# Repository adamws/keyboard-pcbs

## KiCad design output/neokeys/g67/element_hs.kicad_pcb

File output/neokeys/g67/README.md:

## neokeys/g67/element_hs

[layout](element_hs-kle.json) - [PCB](element_hs.kicad_pcb)

{:loading="lazy"}

[Open in keyboard-layout-editor](http://www.keyboard-layout-editor.com/##@@_c=#777777;&=0,0&_c=#cccccc;&=0,1&=0,2&=0,3&=0,4&=0,5&=0,6&=0,7&=0,8&=0,9&=0,10&=0,11&=0,12&_c=#aaaaaa&w:2;&=0,13&=0,14;&@_w:1.5;&=1,0&_c=#cccccc;&=1,1&=1,2&=1,3&=1,4&=1,5&=1,6&=1,7&=1,8&=1,9&=1,10&=1,11&=1,12&_w:1.5;&=1,13&_c=#aaaaaa;&=1,14;&@_w:1.75;&=2,0&_c=#cccccc;&=2,1&=2,2&=2,3&=2,4&=2,5&=2,6&=2,7&=2,8&=2,9&=2,10&=2,11&_c=#777777&w:2.25;&=2,13&_c=#aaaaaa;&=2,14;&@_w:2.25;&=3,0&_c=#cccccc;&=3,2&=3,3&=3,4&=3,5&=3,6&=3,7&=3,8&=3,9&=3,10&=3,11&_c=#aaaaaa&w:1.75;&=3,12&_c=#777777;&=3,13&_c=#aaaaaa;&=3,14;&@_w:1.25;&=4,0&_w:1.25;&=4,1&_w:1.25;&=4,3&_c=#777777&w:6.25;&=4,6&_c=#aaaaaa&w:1.25;&=4,10&_w:1.25;&=4,11&_x:0.5&c=#777777;&=4,12&=4,13&=4,14)

{:loading="lazy"}

## neokeys/g67/hotswap

[layout](hotswap-kle.json) - [PCB](hotswap.kicad_pcb)

{:loading="lazy"}

[Open in keyboard-layout-editor](http://www.keyboard-layout-editor.com/##@@_c=#777777;&=0,0&_c=#cccccc;&=0,1&=0,2&=0,3&=0,4&=0,5&=0,6&=0,7&=0,8&=0,9&=0,10&=0,11&=0,12&_c=#aaaaaa&w:2;&=0,13&=0,14;&@_w:1.5;&=1,0&_c=#cccccc;&=1,1&=1,2&=1,3&=1,4&=1,5&=1,6&=1,7&=1,8&=1,9&=1,10&=1,11&=1,12&_w:1.5;&=1,13&_c=#aaaaaa;&=1,14;&@_w:1.75;&=2,0&_c=#cccccc;&=2,1&=2,2&=2,3&=2,4&=2,5&=2,6&=2,7&=2,8&=2,9&=2,10&=2,11&_c=#777777&w:2.25;&=2,13&_c=#aaaaaa;&=2,14;&@_w:2.25;&=3,0&_c=#cccccc;&=3,2&=3,3&=3,4&=3,5&=3,6&=3,7&=3,8&=3,9&=3,10&=3,11&_c=#aaaaaa&w:1.75;&=3,12&_c=#777777;&=3,13&_c=#aaaaaa;&=3,14;&@_w:1.25;&=4,0&_w:1.25;&=4,1&_w:1.25;&=4,3&_c=#777777&w:6.25;&=4,6&_c=#aaaaaa&w:1.25;&=4,10&_w:1.25;&=4,11&_x:0.5&c=#777777;&=4,12&=4,13&=4,14)

{:loading="lazy"}

## neokeys/g67/soldered

[layout](soldered-kle.json) - [PCB](soldered.kicad_pcb)

{:loading="lazy"}

[Open in keyboard-layout-editor](http://www.keyboard-layout-editor.com/##@@_x:2.75&y:1.5&c=#777777;&=0,0&_c=#cccccc;&=0,1&=0,2&=0,3&=0,4&=0,5&=0,6&=0,7&=0,8&=0,9&=0,10&=0,11&=0,12&_c=#aaaaaa&w:2;&=0,13%0A%0A%0A0,0&=0,15;&@_x:2.75&w:1.5;&=1,0&_c=#cccccc;&=1,1&=1,2&=1,3&=1,4&=1,5&=1,6&=1,7&=1,8&=1,9&=1,10&=1,11&=1,12&_w:1.5;&=1,14%0A%0A%0A1,0&_c=#aaaaaa;&=1,15;&@_x:2.75&w:1.75;&=2,0&_c=#cccccc;&=2,1&=2,2&=2,3&=2,4&=2,5&=2,6&=2,7&=2,8&=2,9&=2,10&=2,11&_c=#777777&w:2.25;&=2,13%0A%0A%0A1,0&_c=#aaaaaa;&=2,15;&@_x:2.75&w:2.25;&=3,0%0A%0A%0A2,0&_c=#cccccc;&=3,2&=3,3&=3,4&=3,5&=3,6&=3,7&=3,8&=3,9&=3,10&=3,11&_c=#aaaaaa&w:1.75;&=3,12&_c=#777777;&=3,14&_c=#aaaaaa;&=3,15;&@_x:2.75&w:1.25;&=4,0%0A%0A%0A3,0&_w:1.25;&=4,1%0A%0A%0A3,0&_w:1.25;&=4,2%0A%0A%0A3,0&_c=#777777&w:6.25;&=4,7%0A%0A%0A3,0&_c=#aaaaaa&w:1.25;&=4,8%0A%0A%0A3,0&_w:1.25;&=4,9%0A%0A%0A3,0&_x:0.5&c=#777777;&=4,12&=4,13&=4,15;&@_x:15.75&y:-6.5&c=#aaaaaa;&=0,13%0A%0A%0A0,1&=0,14%0A%0A%0A0,1;&@_x:20.25&y:1.5&c=#777777&w:1.25&h:2&w2:1.5&h2:1&x2:-0.25;&=2,13%0A%0A%0A1,1;&@_x:19.25&c=#cccccc;&=2,12%0A%0A%0A1,1;&@_c=#aaaaaa&w:1.25;&=3,0%0A%0A%0A2,1&_c=#cccccc;&=3,1%0A%0A%0A2,1;&@_x:2.75&y:1.5&c=#aaaaaa&w:1.5;&=4,0%0A%0A%0A3,1&=4,1%0A%0A%0A3,1&_w:1.5;&=4,2%0A%0A%0A3,1&_c=#777777&w:7;&=4,7%0A%0A%0A3,1&_c=#aaaaaa&w:1.5;&=4,9%0A%0A%0A3,1;&@_x:2.75&w:1.25;&=4,0%0A%0A%0A3,2&_w:1.25;&=4,1%0A%0A%0A3,2&_w:1.25;&=4,2%0A%0A%0A3,2&_c=#777777&w:6.25;&=4,7%0A%0A%0A3,2&_c=#aaaaaa;&=4,8%0A%0A%0A3,2&=4,9%0A%0A%0A3,2&=4,11%0A%0A%0A3,2)

{:loading="lazy"}

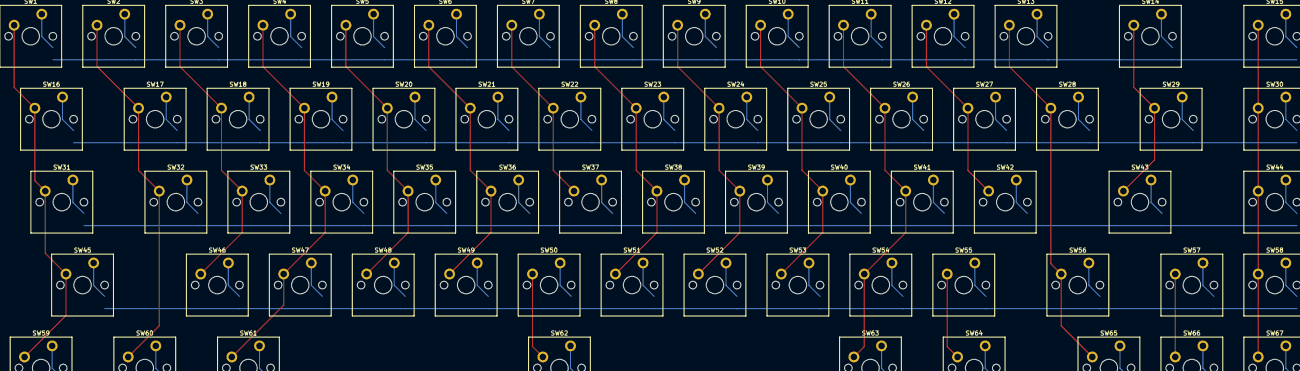
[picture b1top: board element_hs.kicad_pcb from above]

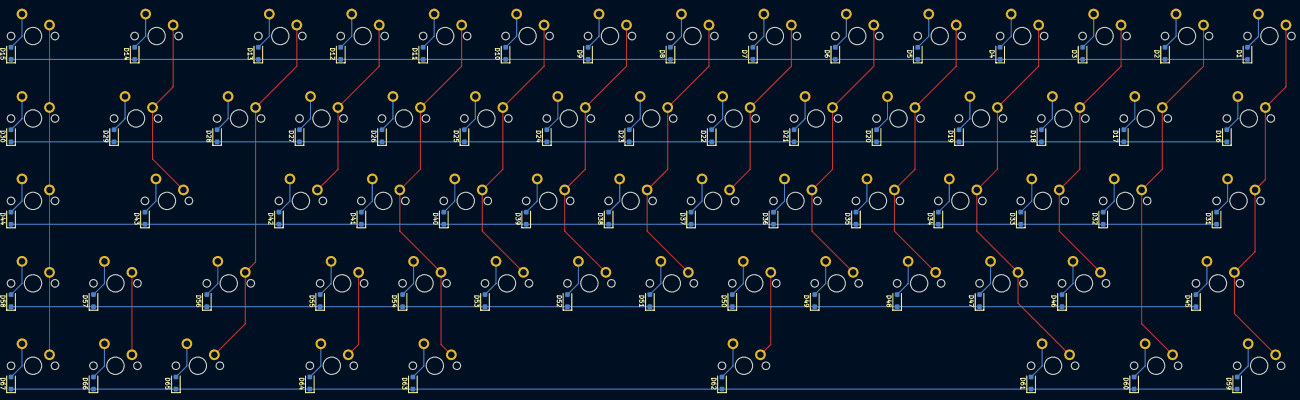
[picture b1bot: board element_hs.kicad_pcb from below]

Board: 2 copper layers, 134 parts (67 on the bottom side), 87 nets.

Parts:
D1, D2, D3, D4, D5, D6, D7, D8, D9, D10, D11, D12, D13, D14, D15, D16, D17, D18, D19, D20, D21, D22, D23, D24, D25, D26, D27, D28, D29, D30, D31, D32, D33, D34, D35, D36, D37, D38, D39, D40, D41, D42, D43, D44, D45, D46, D47, D48, D49, D50, D51, D52, D53, D54, D55, D56, D57, D58, D59, D60, D61, D62, D63, D64, D65, D66, D67: D_SOD-123F
SW1, SW2, SW3, SW4, SW5, SW6, SW7, SW8, SW9, SW10, SW11, SW12, SW13, SW14, SW15, SW16, SW17, SW18, SW19, SW20, SW21, SW22, SW23, SW24, SW25, SW26, SW27, SW28, SW29, SW30, SW31, SW32, SW33, SW34, SW35, SW36, SW37, SW38, SW39, SW40, SW41, SW42, SW43, SW44, SW45, SW46, SW47, SW48, SW49, SW50, SW51, SW52, SW53, SW54, SW55, SW56, SW57, SW58, SW59, SW60, SW61, SW62, SW63, SW64, SW65, SW66, SW67: SW_Cherry_MX_PCB_1.00u

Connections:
COL0: SW1.1, SW16.1, SW31.1, SW45.1, SW59.1
COL1: SW2.1, SW17.1, SW32.1, SW60.1
COL2: SW3.1, SW18.1, SW33.1, SW46.1
COL3: SW4.1, SW19.1, SW34.1, SW47.1, SW61.1
COL4: SW5.1, SW20.1, SW35.1, SW48.1
COL5: SW6.1, SW21.1, SW36.1, SW49.1
COL6: SW7.1, SW22.1, SW37.1, SW50.1, SW62.1
COL7: SW8.1, SW23.1, SW38.1, SW51.1
COL8: SW9.1, SW24.1, SW39.1, SW52.1
COL9: SW10.1, SW25.1, SW40.1, SW53.1
COL10: SW11.1, SW26.1, SW41.1, SW54.1, SW63.1
COL11: SW12.1, SW27.1, SW42.1, SW55.1, SW64.1
COL12: SW13.1, SW28.1, SW56.1, SW65.1
COL13: SW14.1, SW29.1, SW43.1, SW57.1, SW66.1
COL14: SW15.1, SW30.1, SW44.1, SW58.1, SW67.1
unnamed: D1.2, SW1.2
unnamed: D2.2, SW2.2
unnamed: D3.2, SW3.2
unnamed: D4.2, SW4.2
unnamed: D5.2, SW5.2
unnamed: D6.2, SW6.2
unnamed: D7.2, SW7.2
unnamed: D8.2, SW8.2
unnamed: D9.2, SW9.2
unnamed: D10.2, SW10.2
unnamed: D11.2, SW11.2
unnamed: D12.2, SW12.2
unnamed: D13.2, SW13.2
unnamed: D14.2, SW14.2
unnamed: D15.2, SW15.2
unnamed: D16.2, SW16.2
unnamed: D17.2, SW17.2
unnamed: D18.2, SW18.2
unnamed: D19.2, SW19.2
unnamed: D20.2, SW20.2
unnamed: D21.2, SW21.2
unnamed: D22.2, SW22.2
unnamed: D23.2, SW23.2
unnamed: D24.2, SW24.2
unnamed: D25.2, SW25.2
unnamed: D26.2, SW26.2
unnamed: D27.2, SW27.2
unnamed: D28.2, SW28.2
unnamed: D29.2, SW29.2
unnamed: D30.2, SW30.2
unnamed: D31.2, SW31.2
unnamed: D32.2, SW32.2
unnamed: D33.2, SW33.2
unnamed: D34.2, SW34.2
unnamed: D35.2, SW35.2
unnamed: D36.2, SW36.2
unnamed: D37.2, SW37.2
unnamed: D38.2, SW38.2
unnamed: D39.2, SW39.2
unnamed: D40.2, SW40.2
unnamed: D41.2, SW41.2
unnamed: D42.2, SW42.2
unnamed: D43.2, SW43.2
unnamed: D44.2, SW44.2
unnamed: D45.2, SW45.2
unnamed: D46.2, SW46.2
unnamed: D47.2, SW47.2
unnamed: D48.2, SW48.2
unnamed: D49.2, SW49.2
unnamed: D50.2, SW50.2
unnamed: D51.2, SW51.2
unnamed: D52.2, SW52.2
unnamed: D53.2, SW53.2
unnamed: D54.2, SW54.2
unnamed: D55.2, SW55.2
unnamed: D56.2, SW56.2
unnamed: D57.2, SW57.2
unnamed: D58.2, SW58.2
unnamed: D59.2, SW59.2
unnamed: D60.2, SW60.2
unnamed: D61.2, SW61.2
unnamed: D62.2, SW62.2
unnamed: D63.2, SW63.2
unnamed: D64.2, SW64.2
unnamed: D65.2, SW65.2
unnamed: D66.2, SW66.2
unnamed: D67.2, SW67.2
ROW0: D1.1, D2.1, D3.1, D4.1, D5.1, D6.1, D7.1, D8.1, D9.1, D10.1, D11.1, D12.1, D13.1, D14.1, D15.1
ROW1: D16.1, D17.1, D18.1, D19.1, D20.1, D21.1, D22.1, D23.1, D24.1, D25.1, D26.1, D27.1, D28.1, D29.1, D30.1
ROW2: D31.1, D32.1, D33.1, D34.1, D35.1, D36.1, D37.1, D38.1, D39.1, D40.1, D41.1, D42.1, D43.1, D44.1
ROW3: D45.1, D46.1, D47.1, D48.1, D49.1, D50.1, D51.1, D52.1, D53.1, D54.1, D55.1, D56.1, D57.1, D58.1
ROW4: D59.1, D60.1, D61.1, D62.1, D63.1, D64.1, D65.1, D66.1, D67.1
